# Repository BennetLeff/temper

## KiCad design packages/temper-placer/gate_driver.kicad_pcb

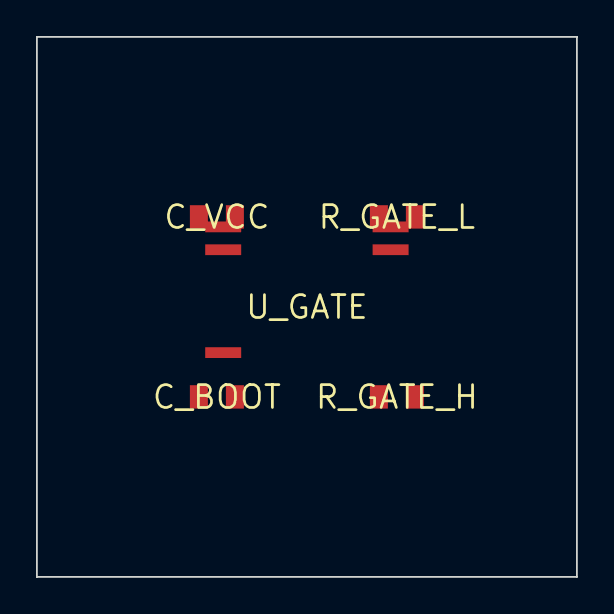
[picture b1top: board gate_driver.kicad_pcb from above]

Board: 2 copper layers, 30.0 x 30.0 mm, 5 parts (0 on the bottom side), 5 nets, no tracks yet.

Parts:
C_BOOT: 10uF; C_0805_2012Metric
C_VCC: 100nF; C_0805_2012Metric
R_GATE_H: 10R; R_0805_2012Metric
R_GATE_L: 10R; R_0805_2012Metric
U_GATE: UCC21550; SOIC-16W_7.5x10.3mm_P1.27mm

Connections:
+15V: C_VCC.1, U_GATE.1
CGND: C_BOOT.2, C_VCC.2, U_GATE.2
GATE_H: R_GATE_H.1, R_GATE_H.2, U_GATE.14
GATE_L: R_GATE_L.1, R_GATE_L.2, U_GATE.16
VCC_BOOT: C_BOOT.1, U_GATE.7

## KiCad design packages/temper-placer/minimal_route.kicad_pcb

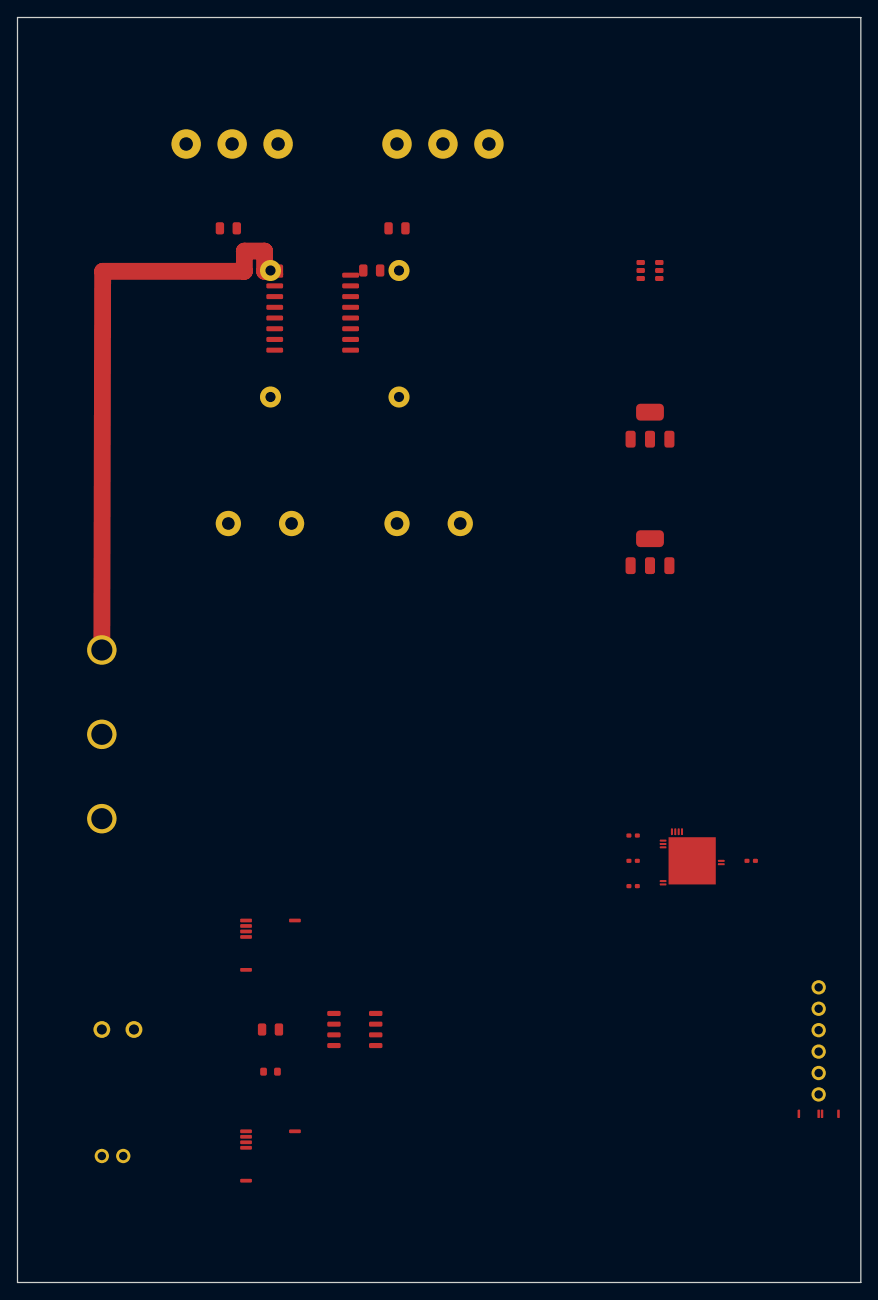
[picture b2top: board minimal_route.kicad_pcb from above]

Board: 4 copper layers, 100.0 x 150.0 mm, 33 parts (0 on the bottom side), 23 nets.

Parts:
C_BOOT: 10uF; C_0805_2012Metric
C_BUS1, C_BUS2: 330uF/400V; CP_Radial_D18.0mm_P7.50mm
C_CT_FILT: 100pF; C_0603_1608Metric
C_MCU_1, C_MCU_2, C_MCU_3: 100nF; C_0402_1005Metric
C_MCU_4: 10uF; C_0402_1005Metric
C_VCC: 10uF; C_0805_2012Metric
D1, D2: 1N5408; D_DO-201AD_P15.24mm_Horizontal
J_AC_IN: IEC_C14; IEC_C14_Male
J_COIL: Coil; PhoenixContact_MCV_1,5_2-G-3.81_1x02_P3.81mm_Vertical
J_DEBUG: Debug; PinHeader_1x06_P2.54mm_Vertical
J_NTC: NTC; PinHeader_1x02_P2.54mm_Vertical
J_USB: USB_C; USB_C_Receptacle_HRO_TYPE-C-31-M-12
MAX31865: MAX31865; TSSOP-20_4.4x6.5mm_P0.65mm
MH1, MH2, MH3, MH4: MountingHole_3.2mm_M3
Q1, Q2: IKW40N120H3; TO-247-3_Horizontal_TabDown
R_BURDEN: 33R; R_0805_2012Metric
R_GATE_H: 4.7R; R_0805_2012Metric
R_GATE_L: 4.7R; R_0805_2012Metric
U_BUCK: LMR51430; SOT-23-6
U_CT: MAX31865; TSSOP-20_4.4x6.5mm_P0.65mm
U_GATE: UCC21550; SOIC-16W_7.5x10.3mm_P1.27mm
U_LDO_3V3: AMS1117-3.3; SOT-223-3_TabPin2
U_LDO_5V: AMS1117-5.0; SOT-223-3_TabPin2
U_MCU: ESP32-S3-WROOM-1; QFN-56-1EP_7x7mm_P0.4mm_EP5.6x5.6mm
U_OPAMP_CT: LM358; SOIC-8_3.9x4.9mm_P1.27mm

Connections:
+3V3: C_MCU_1.1, C_MCU_2.1, C_MCU_3.1, C_MCU_4.1, J_DEBUG.2, MAX31865.20, U_CT.20, U_LDO_3V3.2, U_LDO_3V3.4, U_MCU.1
+5V: U_BUCK.2, U_BUCK.4, U_LDO_3V3.3, U_LDO_5V.2, U_LDO_5V.4, U_OPAMP_CT.7, U_OPAMP_CT.8
+15V: C_VCC.1, U_BUCK.3, U_GATE.1, U_GATE.11, U_LDO_5V.3
AC_L: D1.1, J_AC_IN.1
AC_N: D2.2, J_AC_IN.2
CGND: C_VCC.2, U_GATE.5, U_GATE.6, U_GATE.7, U_GATE.8
DC_BUS+: C_BUS1.1, C_BUS2.1, D1.2, Q1.3
GATE_H: Q1.1, R_GATE_H.1, R_GATE_H.2, U_GATE.15
GATE_L: Q2.1, R_GATE_L.1, R_GATE_L.2, U_GATE.10
GND: C_CT_FILT.2, C_MCU_1.2, C_MCU_2.2, C_MCU_3.2, C_MCU_4.2, J_AC_IN.3, J_COIL.2, J_DEBUG.1, J_NTC.2, J_USB.A1, J_USB.A12, MAX31865.10, R_BURDEN.2, U_BUCK.1, U_BUCK.5, U_BUCK.6, U_CT.10, U_LDO_3V3.1, U_LDO_5V.1, U_MCU.2, U_MCU.57, U_OPAMP_CT.4
I_SENSE: C_CT_FILT.1, R_BURDEN.1, U_MCU.15, U_OPAMP_CT.1, U_OPAMP_CT.2, U_OPAMP_CT.3, U_OPAMP_CT.5, U_OPAMP_CT.6
PGND: C_BUS1.2, C_BUS2.2, Q2.2, U_GATE.12, U_GATE.13
PWM_H: U_GATE.2, U_MCU.13
PWM_L: U_GATE.3, U_MCU.14
SPI_CLK: MAX31865.1, U_CT.1, U_MCU.20
SPI_CS_TEMP: U_CT.4, U_MCU.23
SPI_MISO: MAX31865.3, U_CT.3, U_MCU.22
SPI_MOSI: MAX31865.2, U_CT.2, U_MCU.21
SW_NODE: C_BOOT.2, J_COIL.1, Q1.2, Q2.3, U_GATE.9, U_GATE.16
TEMP_SENSE: J_NTC.1, MAX31865.4
USB_D+: J_USB.A6, U_MCU.40
USB_D-: J_USB.B6, U_MCU.41
VCC_BOOT: C_BOOT.1, U_GATE.14
